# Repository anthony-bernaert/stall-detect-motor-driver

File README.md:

# Motor Driver with Stall Detection
This motor driver safely operates small, brushed 5-24V DC motors up to 2A. It has current-based stall detection that automatically stops driving the motor when the end of travel or an excessive load is sensed.

The board has two inputs that make the motor spin in either direction. When a stall condition is detected, the motor is disabled until both inputs are released. This prevents the stalled motor from heating up and causing the windings to burn out.

In many situations, this removes the need to install mechanical or optical end-stops.

The circuit is built around a DRV8251A motor driver IC, with a few filters and discrete logic components.

>[!NOTE]
>This board was originally intended to be operated by physical buttons. Speed control through PWM is not supported.

## Features
- Robust DRV8251A motor driver chip
- Detects end of travel without adding mechanical or optical end-stops using motor stall current detection
- Operated by two (active-low) inputs, one for each motor direction
- LED indication for both inputs, and for stall conditions
- Simple setup: no microcontroller, no firmware
- Stall threshold, filtering and current limit tuneable with a set of trimpots
- Extra on-board fuse, as a fail-safe
- Open-drain stall status output

## Build overview

Navigate to the releases section to obtain the latest schematic and production files.

## How it works
For an explanation on how the circuit works, see [this page](THEORY.md).

## How to use
### Connections
After assembling the board, power (5-24VDC) must be applied to J1 at pins 'VIN' and 'GND'. The motor leads are to be connected to the same connector, at the pins indicated by 'MOTOR'.

Inputs are to be connected to J2, on pins IN1 and IN2. Inputs are considered active when they are pulled to GND (active-low). If switches are used, place these between GND and IN1/IN2.

### Tuning
The circuit has to be tuned before use:
1. Set the I-LIM trimpot so that the voltage at TP2 matches following formula: $V_{TP2} = I_{max}R_{R6}\cdot 1575\cdot 10^{-6}$.<br />Here, $I_{max}$ is the current limit you want to use for your motor, and $R_{R6}$ is normally 1K. To be safe, you can take $I_{max}$ around the rated stall current of your motor.
2. Then, first turn the T-TRIP trimpot completely clockwise to set the trip time to the maximum
3. Turn the I-TRIP trimpot almost completely clockwise to set the trip current to a very low level
4. Tune the trip current<br />
   a. Be sure that the motor can spin freely<br />
   b. Use IN1/IN2 to spin the motor. If it stalls, release the button, turn I-TRIP a bit counter-clockwise and try again until it no longer stalls.<br />
   c. After finding an acceptable stall threshold, turn I-TRIP a bit more to have some margin.
5. Tune the trip time if necessary<br />
   a. To make the circuit detect stalls earlier, turn the T-TRIP time counter-clockwise<br />
   b. When reducing this time, it's possible that you need to increase the trip current from step 4 a bit, to filter out the initial current peak when the motor starts spinning.

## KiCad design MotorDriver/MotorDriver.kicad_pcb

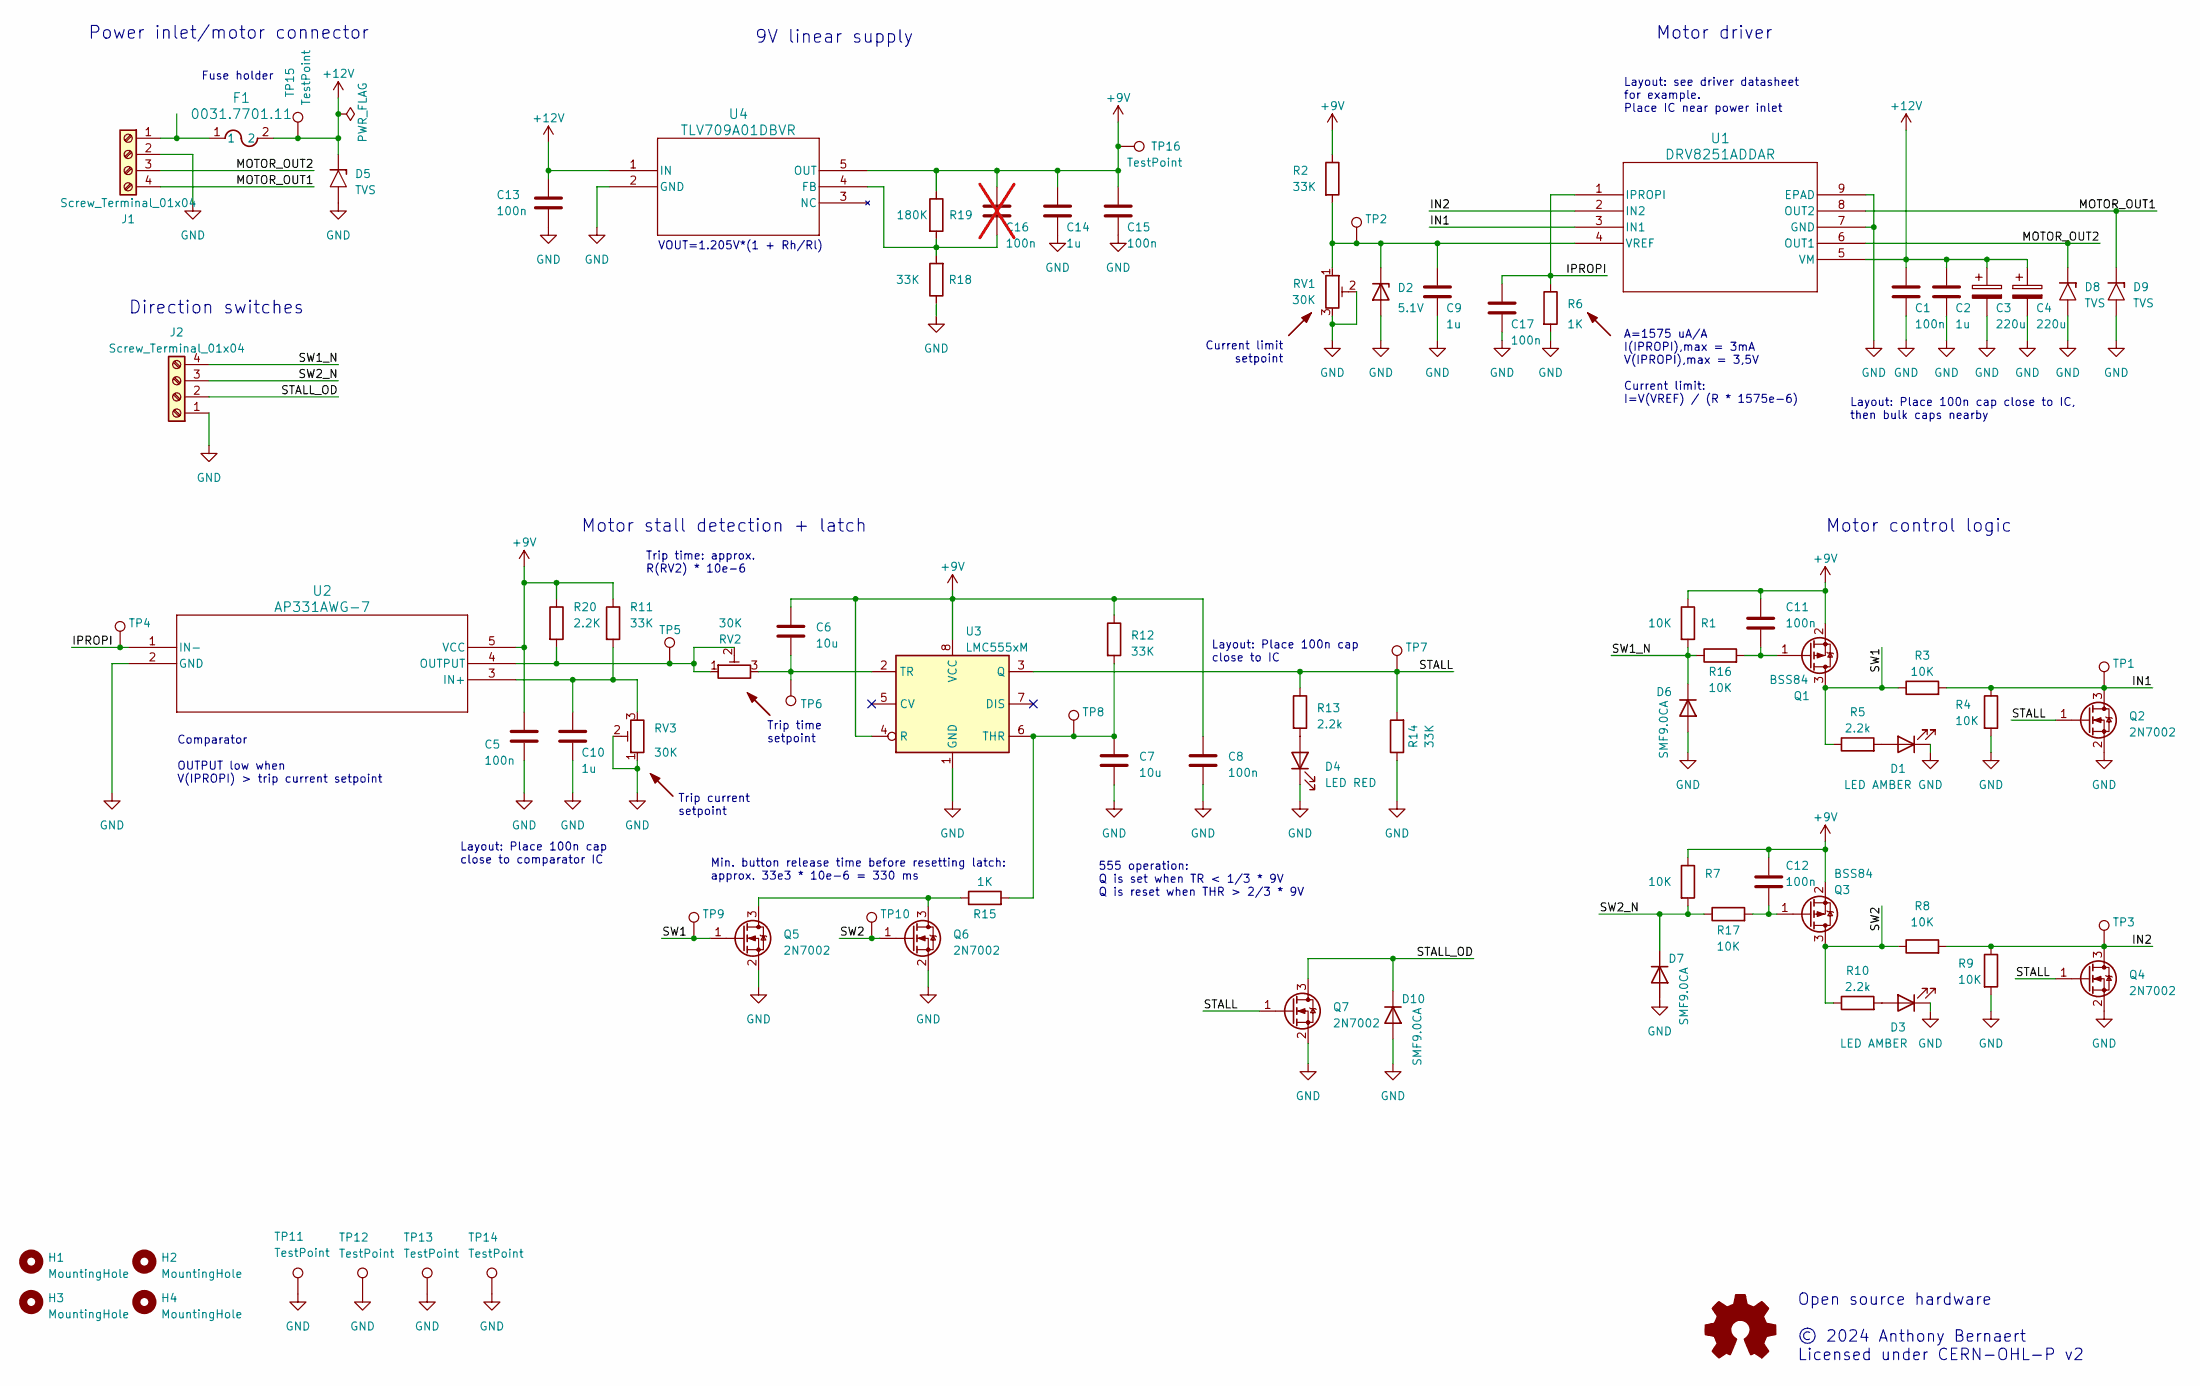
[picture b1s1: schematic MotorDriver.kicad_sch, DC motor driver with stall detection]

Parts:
C1, C5, C8, C11, C12, C13, C15, C17: 100n; C_1206_3216Metric
C2, C9, C10, C14: 1u; C_1206_3216Metric
C3, C4: 220u; CP_Elec_8x10; LCSC C278406
C6, C7: 10u; C_1206_3216Metric
C16: 100n; C_0603_1608Metric; not fitted
D1, D3: LED AMBER; LED_0603_1608Metric; LCSC C5656657
D2: 5.1V; D_SOD-123; LCSC C85181
D4: LED RED; LED_0603_1608Metric; LCSC C965799
D5, D8, D9: TVS; P25_DO-214AC_SMA; LCSC C1974908
D6, D7, D10: SMF9.0CA; D_SOD-123; LCSC C19077504
F1: 0031.7701.11; FUSE_0031.7701.11_SCH
H1, H2, H3, H4: MountingHole; MountingHole_3.5mm
J1, J2: Screw_Terminal_01x04; TerminalBlock_Phoenix_MKDS-1,5-4-5.08_1x04_P5.08mm_Horizont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
Q1, Q3: BSS84; SOT-23; LCSC C82079
Q2, Q4, Q5, Q6, Q7: 2N7002; SOT-23; LCSC C65189
R1, R3, R4, R7, R8, R9, R16, R17: 10K; R_0603_1608Metric
R2, R11, R12, R14, R18: 33K; R_0603_1608Metric
R5, R10, R13: 2.2k; R_0603_1608Metric
R6, R15: 1K; R_0603_1608Metric
R19: 180K; R_0603_1608Metric
R20: 2.2K; R_0603_1608Metric
RV1, RV2, RV3: 30K; Potentiometer_Bourns_TC33X_Vertical; LCSC C6331330
TP1, TP2, TP3, TP4, TP5, TP6, TP7, TP8, TP9, TP10: TestPoint; TestPoint_Pad_D1.5mm
TP11, TP12, TP13, TP14, TP15, TP16: TestPoint; Pin_D1.0mm_L10.0mm
U1: DRV8251ADDAR; SOIC8_DDA_TEX; LCSC C5218844
U2: AP331AWG-7; SOT25_DIO; LCSC C151034
U3: LMC555xM; SOIC-8_3.9x4.9mm_P1.27mm; LCSC C90760
U4: TLV709A01DBVR; SOT-23-5_DBV_TEX; LCSC C22365366

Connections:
+9V: C5.1, C6.1, C8.1, C11.1, C12.1, C14.1, C15.1, C16.1, Q1.2 (S), Q3.2 (S), R1.1, R2.1, R7.1, R11.1, R12.1, R19.1, R20.1, TP16.1, U2.5 (VCC), U3.4 (R), U3.8 (VCC), U4.5 (OUT)
+12V: C1.1, C2.1, C3.1, C4.1, C13.1, D5.1 (K), F1.2, TP15.1, U1.5 (VM), U4.1 (IN)
/IN1: Q2.3 (D), R3.2, R4.1, TP1.1, U1.3 (IN1)
/IN2: Q4.3 (D), R8.2, R9.1, TP3.1, U1.2 (IN2)
/IPROPI: C17.1, R6.1, TP4.1, U1.1 (IPROPI), U2.1 (IN-)
/MOTOR_OUT1: D9.1 (K), J1.4, U1.8 (OUT2)
/MOTOR_OUT2: D8.1 (K), J1.3, U1.6 (OUT1)
/STALL: Q2.1 (G), Q4.1 (G), Q7.1 (G), R13.1, R14.2, TP7.1, U3.3 (Q)
/STALL_OD: D10.1 (K), J2.2, Q7.3 (D)
/SW1: Q1.3 (D), Q5.1 (G), R3.1, R5.1, TP9.1
/SW1_N: D6.1 (K), J2.4, R1.2, R16.1
/SW2: Q3.3 (D), Q6.1 (G), R8.1, R10.1, TP10.1
/SW2_N: D7.1 (K), J2.3, R7.2, R17.1
GND: C1.2, C2.2, C3.2, C4.2, C5.2, C7.2, C8.2, C9.2, C10.2, C13.2, C14.2, C15.2, C17.2, D1.1 (K), D2.2 (A), D3.1 (K), D4.1 (K), D5.2 (A), D6.2 (A), D7.2 (A), D8.2 (A), D9.2 (A), D10.2 (A), J1.2, J2.1, Q2.2 (S), Q4.2 (S), Q5.2 (S), Q6.2 (S), Q7.2 (S), R4.2, R6.2, R9.2, R14.1, R18.1, RV1.2, RV1.3, RV3.1, RV3.2, TP11.1, TP12.1, TP13.1, TP14.1, U1.7 (GND), U1.9 (EPAD), U2.2 (GND), U3.1 (GND), U4.2 (GND)
unnamed: D1.2 (A), R5.2
unnamed: C9.1, D2.1 (K), R2.2, RV1.1, TP2.1, U1.4 (VREF)
unnamed: D3.2 (A), R10.2
unnamed: D4.2 (A), R13.2
unnamed: F1.1, J1.1
unnamed: C11.2, Q1.1 (G), R16.2
unnamed: C12.2, Q3.1 (G), R17.2
unnamed: Q5.3 (D), Q6.3 (D), R15.1
unnamed: C10.1, R11.2, RV3.3, U2.3 (IN+)
unnamed: R20.2, RV2.1, RV2.2, TP5.1, U2.4 (OUTPUT)
unnamed: C7.1, R12.2, R15.2, TP8.1, U3.6 (THR)
unnamed: C6.2, RV2.3, TP6.1, U3.2 (TR)
unnamed: C16.2, R18.2, R19.2, U4.4 (FB)

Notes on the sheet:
9V linear supply
Layout: see driver datasheet for example. Place IC near power inlet
Comparator OUTPUT low when V(IPROPI) > trip current setpoint
Current limit setpoint
Layout: Place 100n cap close to comparator IC
VOUT=1.205V*(1 + Rh/Rl)
Layout: Place 100n cap close to IC
Trip time setpoint
Motor driver
Power inlet/motor connector
Min. button release time before resetting latch: approx. 33e3 * 10e-6 = 330 ms
Trip time: approx. R(RV2) * 10e-6
555 operation: Q is set when TR < 1/3 * 9V Q is reset when THR > 2/3 * 9V
Direction switches
Open source hardware © 2024 Anthony Bernaert Licensed under CERN-OHL-P v2
Motor stall detection + latch
Layout: Place 100n cap close to IC, then bulk caps nearby
Trip current setpoint
Fuse holder
A=1575 uA/A I(IPROPI),max = 3mA V(IPROPI),max = 3,5V Current limit: I=V(VREF) / (R * 1575e-6)
Motor control logic

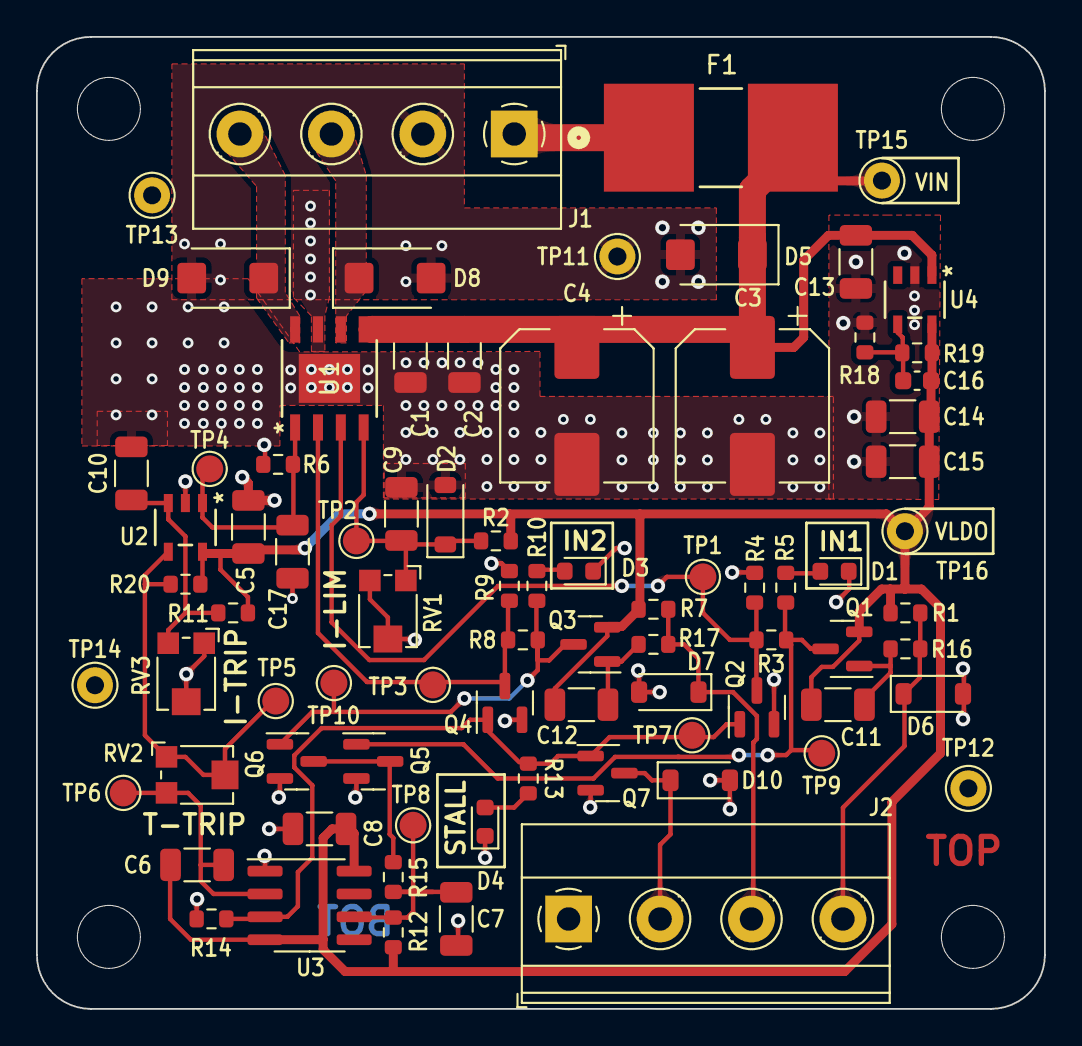
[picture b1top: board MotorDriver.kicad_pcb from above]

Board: 2 copper layers, 56.0 x 54.0 mm, 84 parts (0 on the bottom side), 27 nets.

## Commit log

2024-10-07 Add license
2024-11-04 Add gitignore for KiCad project
2024-11-04 Check-in of first revision
2025-03-25 Add LCSC order numbers

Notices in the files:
MotorDriver/MotorDriver.kicad_pcb:
© 2024 A. Bernaert
